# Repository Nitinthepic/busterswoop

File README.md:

# Busterswoop

A WIP fork of [SuperFola's Arkenswoop](https://github.com/SuperFola/arkenswoop),
which is a fork of [jimmerricks's Swoop](https://github.com/jimmerricks/swoop),
which is a fork of [David Barr's Sweep](https://github.com/davidphilipbarr/Sweep),
which is itself based on the fabulous [Ferris by Pierre Chevalier](https://github.com/pierrechevalier83/ferris).

| Front | Back |
| :---: | :---: |
|  |  |

### Features

⭕ Low profile Kailh Choc switches  
⭕ Hotswap  
⭕ Oled screens  
⭕ Power switch for battery management  
⭕ Bluetooth support w/ nice!nano  
⭕ 3D cased assembled with M2 screws 

### Components list

To build and use an Busterswoop you will need:

* 1× PCB Kit (1.6mm thickness when ordering)
* 2× promicro compatible boards or 2 nice!nanos.
* 36× Kailh Choc v1 switches
* 36× Kailh Choc hotswap sockets (PG1350)
* 36× keycaps
* 1-2× OLED LCD Display 128x32 SSD1306 (optional)
* 1-2x Female 4-Pin Headers (optional)
* 4 or 8x Male Header Pins (optional)
* 2× reset switches (optional; B3U-1000P(M))
* Some little rubber feet/bumpers (minimum of 4 on each side)
* 2× power switches (wireless only; MSK 12C02)
* 2× lipo batteries (wireless only; 301230 or 301228)
* 1× TRRS (not TRS!) cable (wired only)
* 2× TRRS Jack [PJ-320A] (wired only)
* 1× USB Cable

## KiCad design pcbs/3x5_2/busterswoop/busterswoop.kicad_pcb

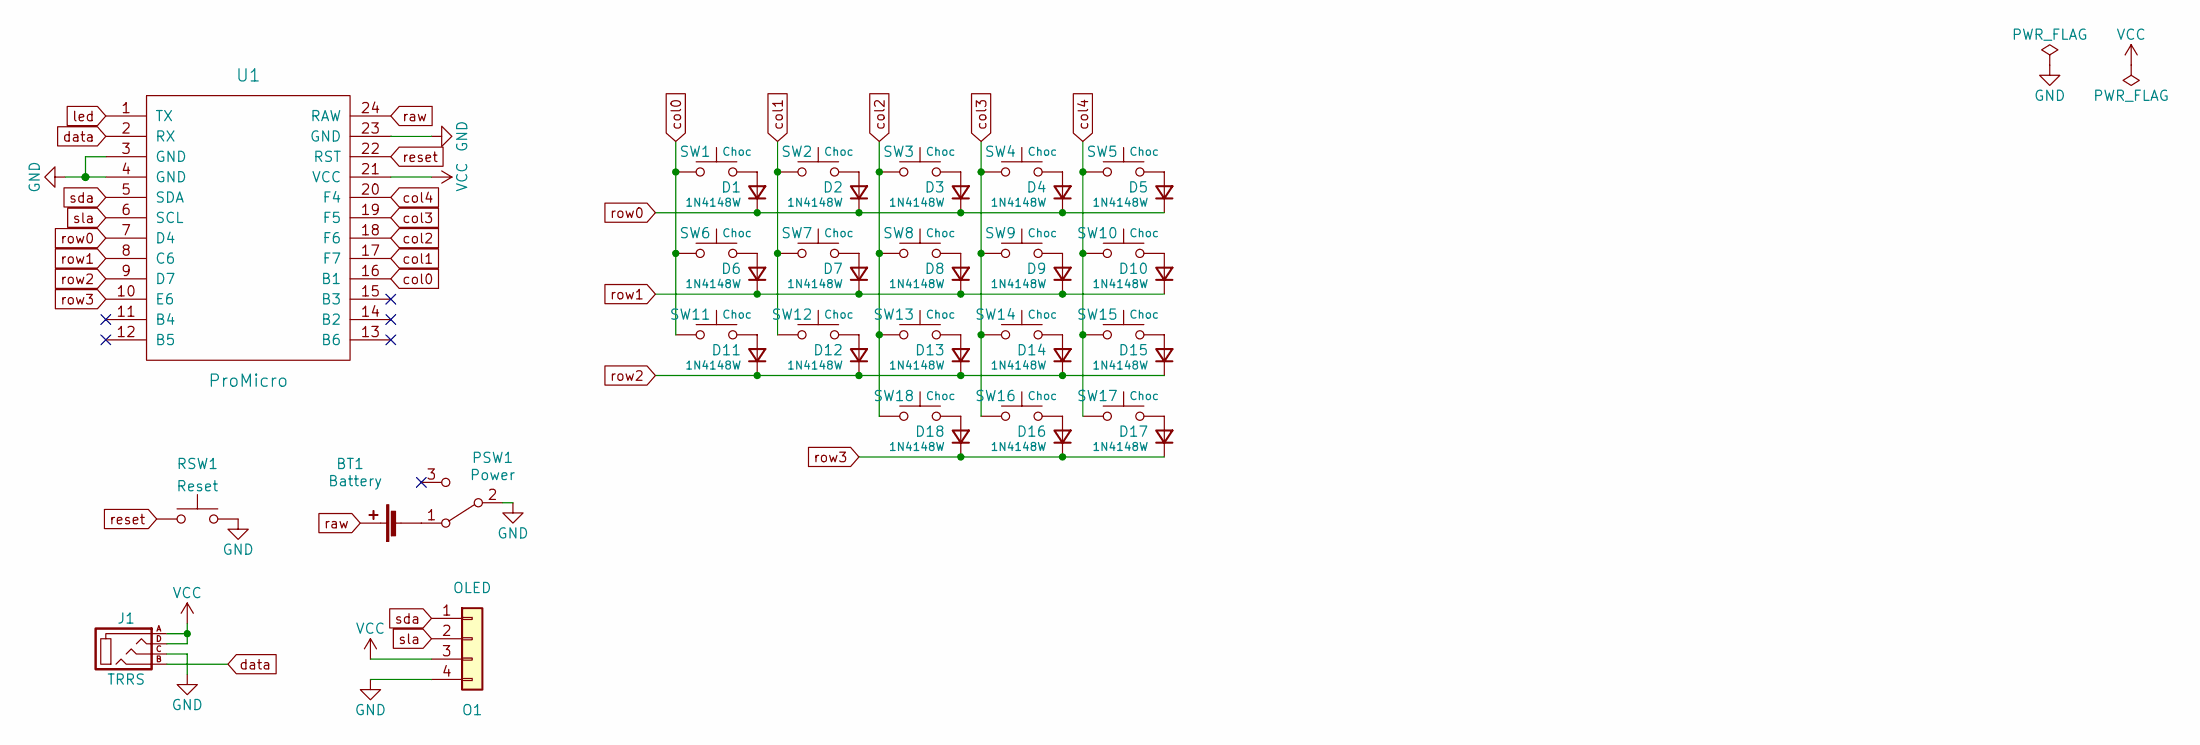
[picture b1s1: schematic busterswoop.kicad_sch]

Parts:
BT1: Battery; Battery_pads_reversible
D1, D2, D3, D4, D5, D6, D7, D8, D9, D10, D11, D12, D13, D14, D15, D16, D17, D18: 1N4148W; D3_SMD
J1: TRRS; TRRS-3pin
O1: OLED; OLED_jumpers
PSW1: Power
RSW1: Reset
SW1, SW2, SW3, SW4, SW5, SW6, SW7, SW8, SW9, SW10, SW11, SW12, SW13, SW14, SW15, SW16, SW17, SW18: Choc; Kailh-pg1350-socket-reversible
U1: ProMicro; ProMicro_jumpers

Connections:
GND: J1.C, O1.4, PSW1.2 (B), RSW1.2, U1.3 (GND), U1.4 (GND), U1.23 (GND)
unnamed: BT1.2 (-), PSW1.1 (A)
unnamed: D1.2 (A), SW1.2
unnamed: D2.2 (A), SW2.2
unnamed: D3.2 (A), SW3.2
unnamed: D4.2 (A), SW4.2
unnamed: D5.2 (A), SW5.2
unnamed: D6.2 (A), SW6.2
unnamed: D7.2 (A), SW7.2
unnamed: D8.2 (A), SW8.2
unnamed: D9.2 (A), SW9.2
unnamed: D10.2 (A), SW10.2
unnamed: D11.2 (A), SW11.2
unnamed: D12.2 (A), SW12.2
unnamed: D13.2 (A), SW13.2
unnamed: D14.2 (A), SW14.2
unnamed: D15.2 (A), SW15.2
unnamed: D16.2 (A), SW16.2
unnamed: D17.2 (A), SW17.2
unnamed: D18.2 (A), SW18.2
VCC: J1.A, J1.D, O1.3, U1.21 (VCC)
col0: SW1.1, SW6.1, SW11.1, U1.16 (B1)
col1: SW2.1, SW7.1, SW12.1, U1.17 (F7)
col2: SW3.1, SW8.1, SW13.1, SW18.1, U1.18 (F6)
col3: SW4.1, SW9.1, SW14.1, SW16.1, U1.19 (F5)
col4: SW5.1, SW10.1, SW15.1, SW17.1, U1.20 (F4)
data: J1.B, U1.2 (RX)
led: U1.1 (TX)
raw: BT1.1 (+), U1.24 (RAW)
reset: RSW1.1, U1.22 (RST)
row0: D1.1 (K), D2.1 (K), D3.1 (K), D4.1 (K), D5.1 (K), U1.7 (D4)
row1: D6.1 (K), D7.1 (K), D8.1 (K), D9.1 (K), D10.1 (K), U1.8 (C6)
row2: D11.1 (K), D12.1 (K), D13.1 (K), D14.1 (K), D15.1 (K), U1.9 (D7)
row3: D16.1 (K), D17.1 (K), D18.1 (K), U1.10 (E6)
sda: O1.1, U1.5 (SDA)
sla: O1.2, U1.6 (SCL)

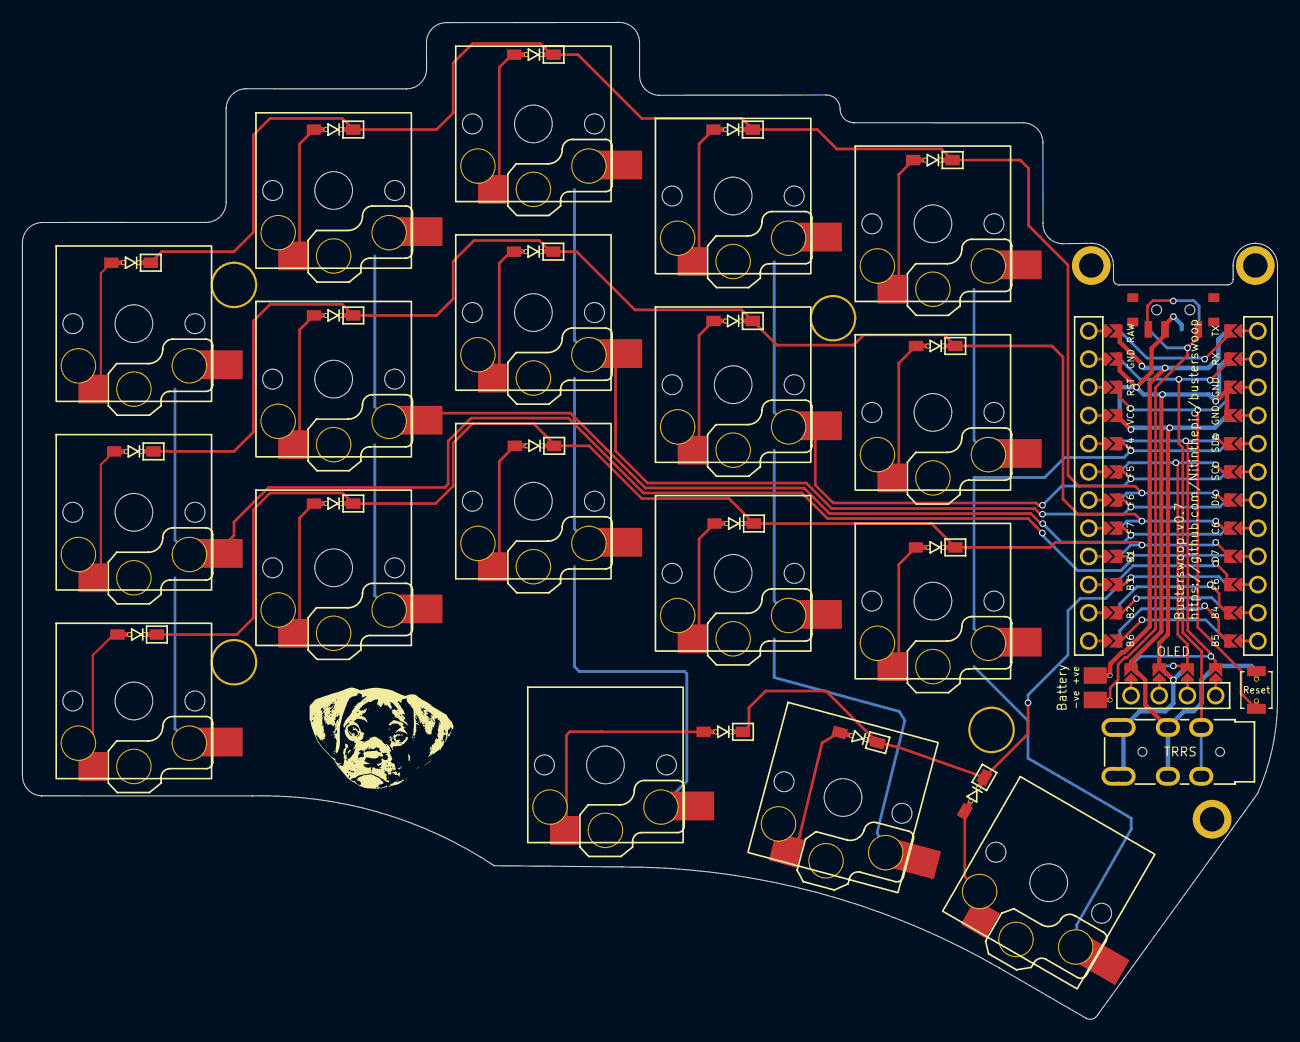
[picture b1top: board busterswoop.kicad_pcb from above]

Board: 2 copper layers, 113.1 x 89.8 mm, 49 parts (1 on the bottom side), 35 nets.

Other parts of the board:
H1, H2, H3, H4: M2 Hole; M2_hole_4.2mm
Ref**: Val**; M2_hole_3.5mm
Ref**#2, Ref**#3: Val**; M2_hole_3.5mm

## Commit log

2023-11-13 First Big Commit I have added in the new thumb key, updated the schematic and footprints to match Kailh choc reversibles I have also finished modelling 3D cases for the keyboard, added a silkscreen o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
2023-11-13 updated readme - WIP
2023-11-13 Update README.md - Fixed Features section
2023-12-07 added new stls and images
2023-12-07 Update README.md
    removed image section and changed image reference paths
2023-12-07 added new images and rotated finished build
